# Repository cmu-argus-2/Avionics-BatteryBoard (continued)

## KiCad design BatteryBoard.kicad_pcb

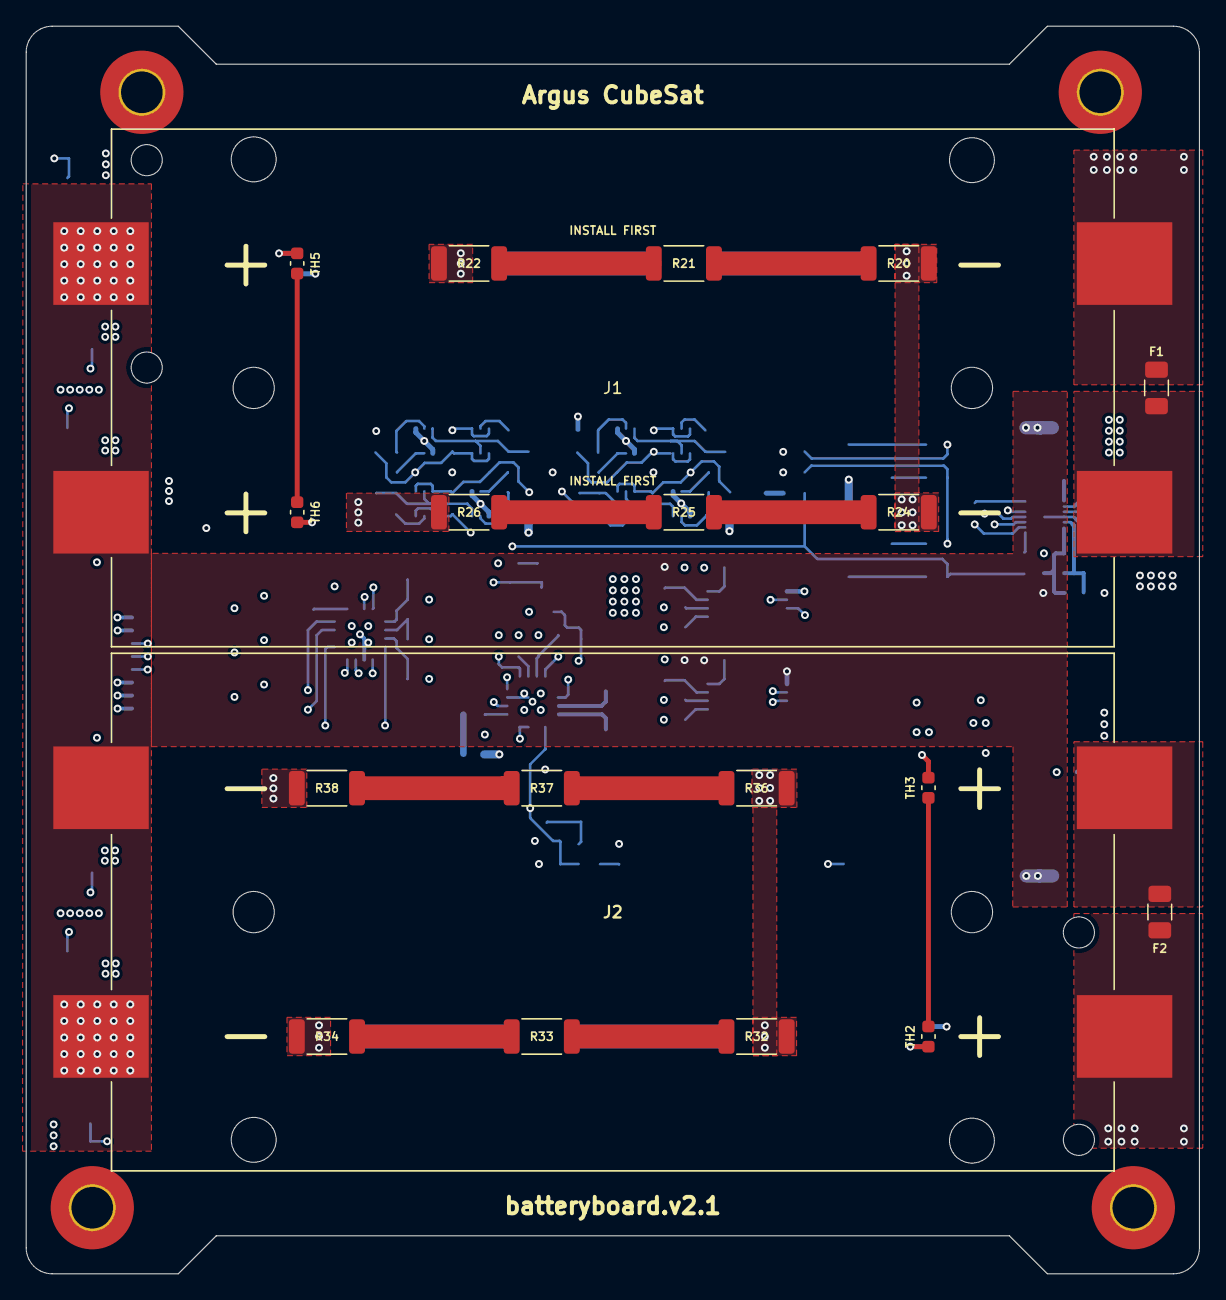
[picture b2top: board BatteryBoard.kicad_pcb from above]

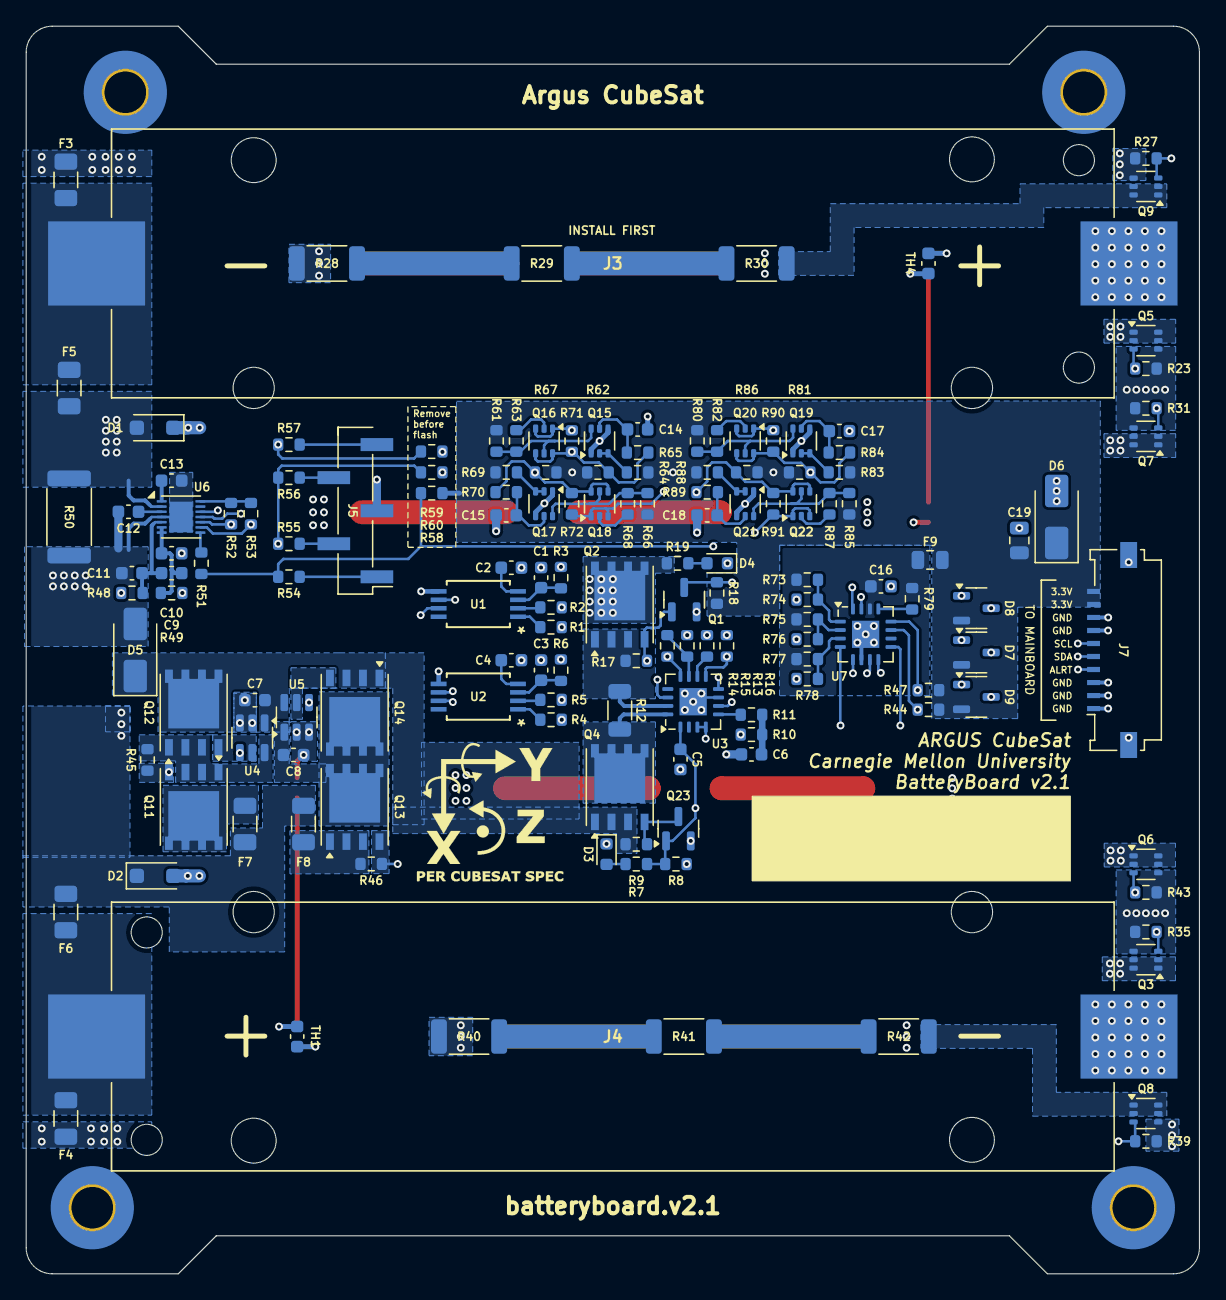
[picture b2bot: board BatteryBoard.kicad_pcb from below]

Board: 4 copper layers, 90.2 x 95.9 mm, 173 parts (149 on the bottom side), 115 nets.

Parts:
C1, C3, C7, C8, C11, C16: 0.1uF; C_0603_1608Metric
C2, C4, C14, C15, C17, C18: 10nF; C_0603_1608Metric
C5, C6: 1uF; C_0603_1608Metric
C9, C10: 1nF; C_0603_1608Metric
C12, C13: 0.47uF; C_0603_1608Metric
C19: 10uF; C_0805_2012Metric
D1, D2: 10V Vrm; D_SOD-123F
D3, D4: GREEN; LED_0603_1608Metric
D5: 10V; D_SMA
D6: 4.7V; D_SMA
D7, D8, D9: MMBD452LT1G; SOT-23-3
F1, F2, F3, F4, F5, F6: 10A; Fuse_1206_3216Metric
F7, F8: 6A; Fuse_1206_3216Metric
F9: 1A; Fuse_0805_2012Metric
H1, H2, H3, H4: MountingHole_Pad; MountingHole_3.2mm_M3_Pad_TopBottom
J1, J2: Keystone-1048; BAT_1048
J3, J4: Keystone-1042; Keystone_1042
J5: Fuel Gauge Programming Header; PinHeader_1x05_P2.54mm_Vertical_SMD_Pin1Left
J7: 200528-0100; Molex_200528-0100_1x10-1MP_P1.00mm_Horizontal
Q1, Q23: IRLML2803; SOT-23
Q2, Q4, Q11, Q12, Q13, Q14: SIRA99DP-T1-GE3; PowerPAK_SO-8_Single
Q3, Q5, Q6, Q7, Q8, Q9: Si1442DH; SOT-363_SC-70-6
Q15, Q17, Q19, Q21: NX3008NBKS; SOT-363_SC-70-6
Q16, Q18, Q20, Q22: MBT2222ADW1T1; SOT-363_SC-70-6
R1, R2, R4, R5, R51: 1k; R_0603_1608Metric
R3, R6: 470R; R_0603_1608Metric
R7, R19: 2.7k; R_0603_1608Metric
R8, R9, R11, R14, R16, R17, R18, R23, R27, R31, R35, R39, R43, R58, R61, R62, R66, R67, R73, R74, R75, R76, R77, R78, R79, R80, R81, R85, R86: 10k; R_0603_1608Metric
R10, R45, R46, R64, R69, R83, R88: 100k; R_0603_1608Metric
R12: 0.05R; R_1206_3216Metric
R13, R59, R60: 0R; R_0603_1608Metric
R15, R52, R53: 30k; R_0603_1608Metric
R20, R21, R22, R24, R25, R26, R28, R29, R30, R32, R33, R34, R36, R37, R38, R40, R41, R42: 10R; R_2010_5025Metric
R44, R47: 470k; R_0603_1608Metric
R48: 10R; R_0603_1608Metric
R49: 100R; R_0603_1608Metric
R50: 10m; R_2512_6332Metric
R54: 51.1k; R_0603_1608Metric
R55, R56, R57: 150R; R_0603_1608Metric
R63, R68, R82, R87: 680R; R_0603_1608Metric
R65, R70, R84, R89: 200k; R_0603_1608Metric
R71, R72, R90, R91: DNI (0R); R_0603_1608Metric
TH1, TH2, TH3, TH4, TH5, TH6: 10k 3435k; C_0603_1608Metric
U1, U2: S-8209AAA-T8T1U; TSSOP8-E-PKG_FT008-A-P-SD-1.2_ABL
U3: MAX4211B/E; QFN-16-1EP_4x4mm_P0.65mm_EP2.1x2.1mm
U4, U5: LTC4412xS6; TSOT-23-6
U6: MAX17205; TDFN-14-1EP_3x3mm_P0.4mm_EP1.78x2.35mm
U7: MAX7310; QFN-16-1EP_4x4mm_P0.65mm_EP2.1x2.1mm

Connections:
+3V3: C19.1, D6.1 (K), D7.2 (K), D8.2 (K), D9.2 (K), F9.2, J7.9, J7.10, R18.2, R44.1, R47.1, R58.2, R61.1, R62.1, R64.1, R66.1, R67.1, R69.1, R80.1, R81.1, R83.1, R85.1, R86.1, R88.1
/Battery Bus Detection/BATT_M: C3.2, C4.2, D1.1 (K), D2.2 (A), J1.2 (POS), J1.4 (POS), J2.1 (NEG), J2.3 (NEG), J3.2 (POS), J4.1 (NEG), R3.1, R49.1, U2.5 (VSS)
/Battery Bus Detection/BATT_N: C1.2, C2.2, C10.2, D1.2 (A), F5.2, R1.2, R2.2, R50.2, U1.5 (VSS), U6.2 (CSP)
/Battery Bus Detection/BATT_P: D2.1 (K), F6.2, F7.1, F8.2, R6.1, R48.1
/Battery Bus Detection/CHARGE_EN: Q11.4 (G), R45.2, U2.7 (CO)
/Battery Bus Detection/DISCHARGE_EN: Q13.4 (G), R46.2, U2.6 (DO)
/Battery Bus Protection/CHARGE_ACTIVE: R44.2, U4.4 (STAT), U7.11 (IO6)
/Battery Bus Protection/DISCHARGE_ACTIVE: R47.2, U5.4 (STAT), U7.12 (IO7)
/Battery Monitor/A: J5.1, R54.2
/Battery Monitor/C: J5.5, R57.2
/Battery Monitor/D: J5.4, R56.2
/Battery Monitor/DQ: J5.2, R55.2
/Battery Monitor/I2C Protection/SCL_DEVICE: Q16.4 (E2), Q16.6 (C1), R59.2, R62.2, R65.1, R71.1
/Battery Monitor/I2C Protection/SDA_DEVICE: Q18.4 (E2), Q18.6 (C1), R60.1, R67.2, R70.1, R72.1
/Battery Monitor/SCL: R57.1, R59.1, U6.11 (SCL)
/Battery Monitor/SDA: R55.1, R56.1, R60.2, U6.12 (SDA)
/Battery Temperature Protection/CB-RESET: R16.2, U3.9 (CIN2-), U7.7 (IO2)
/Battery Temperature Protection/HEATER_ENABLE0: Q5.3 (G), Q7.3 (G), Q9.3 (G), R23.2, R27.2, R31.2, U7.8 (IO3)
/Battery Temperature Protection/HEATER_ENABLE1: Q3.3 (G), Q6.3 (G), Q8.3 (G), R35.2, R39.2, R43.2, U7.9 (IO4)
/Battery Temperature Protection/ON/~OFF: C5.1, Q23.1 (G), R7.1, R8.2, U3.1 (VCC), U7.4 (IO0)
/Battery Temperature Protection/~FAULT: Q1.3 (D), R18.1, U7.5 (IO1)
/IO Expander/AD0: R73.2, R74.1, U7.1 (AD0)
/IO Expander/AD1: R75.2, R76.1, U7.2 (AD1)
/IO Expander/AD2: R77.2, R78.1, U7.3 (AD2)
/IO Expander/SCL: Q20.4 (E2), Q20.6 (C1), R81.2, R84.1, R90.1, U7.15 (SCL)
/IO Expander/SDA: Q22.4 (E2), Q22.6 (C1), R86.2, R89.1, R91.1, U7.16 (SDA)
/Interfaces/ALERT: D9.3 (common), J7.4, R51.2, R54.1, R58.1
/Interfaces/SCL_BUS: D8.3 (common), J7.6, Q16.1 (E1), Q16.3 (C2), Q20.1 (E1), Q20.3 (C2), R71.2, R90.2
/Interfaces/SDA_BUS: D7.3 (common), J7.5, Q18.1 (E1), Q18.3 (C2), Q22.1 (E1), Q22.3 (C2), R72.2, R91.2
GND: C5.2, C14.2, C15.2, C16.2, C17.2, C18.2, C19.2, D3.1 (K), D4.1 (K), D6.2 (A), D7.1 (A), D8.1 (A), D9.1 (A), H1.1, H2.1, H3.1, H4.1, J7.1, J7.2, J7.3, J7.7, J7.8, J7.MP (MountPin), Q1.2 (S), Q15.1 (S), Q15.4 (S), Q17.1 (S), Q17.4 (S), Q19.1 (S), Q19.4 (S), Q21.1 (S), Q21.4 (S), Q23.2 (S), R8.1, R10.1, R15.1, R16.1, R74.2, R76.2, R78.2, U3.7 (GND), U3.17 (GND), U7.6 (GND), U7.17 (GND)
unnamed: C6.1, R10.2, R11.2
unnamed: D3.2 (A), R7.2
unnamed: D4.2 (A), R19.1
unnamed: F1.1, J1.1 (NEG)
unnamed: F1.2, F3.1, J1.3 (NEG)
unnamed: F2.1, J2.2 (POS)
unnamed: F2.2, F4.1, J2.4 (POS)
unnamed: F8.1, Q13.1 (S), Q13.2 (S), Q13.3 (S), R46.1
unnamed: F3.2, F5.1, J3.1 (NEG)
unnamed: F4.2, F6.1, J4.2 (POS)
unnamed: Q1.1 (G), Q2.4 (G), R17.1, U3.3 (LE), U3.4 (COUT1), U3.6 (COUT2)
unnamed: Q3.1 (D), Q3.2 (D), Q3.5 (D), Q3.6 (D), R34.1
unnamed: Q4.5 (D), R12.1, U3.16 (RS+)
unnamed: Q5.1 (D), Q5.2 (D), Q5.5 (D), Q5.6 (D), R22.1
unnamed: Q6.1 (D), Q6.2 (D), Q6.5 (D), Q6.6 (D), R38.1
unnamed: Q7.1 (D), Q7.2 (D), Q7.5 (D), Q7.6 (D), R26.1
unnamed: Q8.1 (D), Q8.2 (D), Q8.5 (D), Q8.6 (D), R42.1
unnamed: Q9.1 (D), Q9.2 (D), Q9.5 (D), Q9.6 (D), R30.1
unnamed: F7.2, Q11.5 (D)
unnamed: Q12.4 (G), U4.5 (GATE)
unnamed: C8.1, Q13.5 (D), Q14.5 (D), U5.1 (VIN)
unnamed: Q14.4 (G), U5.5 (GATE)
unnamed: Q15.6 (D), Q16.5 (B2), R61.2, R63.2
unnamed: Q15.2 (G), Q15.3 (D), R64.2
unnamed: C14.1, Q15.5 (G), R65.2
unnamed: Q16.2 (B1), R63.1
unnamed: Q17.6 (D), Q18.5 (B2), R66.2, R68.2
unnamed: Q17.2 (G), Q17.3 (D), R69.2
unnamed: C15.1, Q17.5 (G), R70.2
unnamed: Q18.2 (B1), R68.1
unnamed: Q19.6 (D), Q20.5 (B2), R80.2, R82.2
unnamed: Q19.2 (G), Q19.3 (D), R83.2
unnamed: C17.1, Q19.5 (G), R84.2
unnamed: Q20.2 (B1), R82.1
unnamed: Q21.6 (D), Q22.5 (B2), R85.2, R87.2
unnamed: Q21.2 (G), Q21.3 (D), R88.2
unnamed: C18.1, Q21.5 (G), R89.2
unnamed: Q22.2 (B1), R87.1
unnamed: Q4.4 (G), Q23.3 (D), R9.1
unnamed: R20.1, R21.2
unnamed: R21.1, R22.2
unnamed: R24.1, R25.2
unnamed: R25.1, R26.2
unnamed: R28.1, R29.2
unnamed: R29.1, R30.2
unnamed: R32.1, R33.2
unnamed: R33.1, R34.2
unnamed: R36.1, R37.2
unnamed: R37.1, R38.2
unnamed: R40.1, R41.2
unnamed: R41.1, R42.2
unnamed: TH1.2, TH2.1
unnamed: TH2.2, TH3.1
unnamed: TH4.2, TH5.1
unnamed: TH5.2, TH6.1
unnamed: C2.1, U1.4 (CDT)
unnamed: R4.2, U1.7 (CO)
unnamed: R1.1, U1.1 (CTLC)
unnamed: R2.1, U1.2 (CTLD)
unnamed: R5.2, U1.6 (DO)
unnamed: C1.1, R3.2, U1.3 (VDD)
unnamed: C4.1, U2.4 (CDT)
unnamed: R4.1, U2.1 (CTLC)
unnamed: R5.1, U2.2 (CTLD)
unnamed: C3.1, R6.2, U2.3 (VDD)
unnamed: R13.1, U3.10 (CIN1+)
unnamed: R14.1, R15.2, U3.11 (CIN1-)
unnamed: R14.2, U3.8 (CIN2+), U3.12 (REF)
unnamed: R11.1, U3.5 (INHIBIT)
unnamed: R13.2, U3.14 (IOUT)
unnamed: Q2.1 (S), Q2.2 (S), Q2.3 (S), R12.2, R17.2, U3.15 (RS-)
unnamed: Q11.1 (S), Q11.2 (S), Q11.3 (S), Q12.1 (S), Q12.2 (S), Q12.3 (S), R45.1, U4.6 (SENSE)
unnamed: R53.2, TH4.1, U6.9 (AIN1)
unnamed: R52.2, TH1.1, U6.10 (AIN2)
unnamed: R51.1, U6.8 (ALRT1)
unnamed: C9.2, C10.1, R49.2, U6.6 (CELL2), U6.7 (CELL1)
unnamed: C12.1, U6.3 (REG2)
unnamed: C13.1, U6.1 (REG3)
unnamed: R52.1, R53.1, U6.14 (THRM)
unnamed: C9.1, C11.1, R48.2, U6.5 (VBATT)
unnamed: C16.1, F9.1, R73.1, R75.1, R77.1, R79.2, U7.14 (V+)
unnamed: R79.1, U7.13 (~RESET)
SYSTEM_VDD: C7.1, D5.1 (K), Q4.1 (S), Q4.2 (S), Q4.3 (S), Q12.5 (D), Q14.1 (S), Q14.2 (S), Q14.3 (S), R9.2, U4.1 (VIN), U5.6 (SENSE)
SYSTEM_VSS: C7.2, C8.2, C11.2, C12.2, C13.2, D5.2 (A), J5.3, Q3.4 (S), Q5.4 (S), Q6.4 (S), Q7.4 (S), Q8.4 (S), Q9.4 (S), R23.1, R27.1, R31.1, R35.1, R39.1, R43.1, R50.1, TH3.2, TH6.2, U4.2 (GND), U4.3 (CTL), U5.2 (GND), U5.3 (CTL), U6.4 (CSN), U6.15 (GND)
VBUS: C6.2, Q2.5 (D), R19.2, R20.2, R24.2, R28.2, R32.2, R36.2, R40.2

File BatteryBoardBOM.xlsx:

Reference | Value | Datasheet | Footprint | Qty | DNP | MFR Part Number
C1,C3,C7,C8,C11 | 0.1uF | ~ | Capacitor_SMD:C_0603_1608Metric | 5 |  | CL10B104KA8NNNC | 25
C2,C4,C14,C15 | 10nF | ~ | Capacitor_SMD:C_0603_1608Metric | 4 |  | CL10B103KO8WPNC | 20
C9,C10 | 1nF | ~ | Capacitor_SMD:C_0603_1608Metric | 2 |  | C0603C102J8HACAUTO | 10
C12,C13 | 0.47uF | ~ | Capacitor_SMD:C_0603_1608Metric | 2 |  | CL10B474KO8VPJC | 10
C19 | 10uF | ~ | Capacitor_SMD:C_0805_2012Metric | 1 |  | GRM21BR71A106KA73L | 5
D1,D2 | BAT60JFILM | ~ | Diode_SMD:D_SOD-323_HandSoldering | 2 |  | BAT60JFILM | 10
D3,D4,D10 | GREEN | ~ | LED_SMD:LED_0603_1608Metric | 3 |  | 150060GS75000 | 15
D5 | 10V | ~ | Diode_SMD:D_SMA | 1 |  | PTVS10VZ1USKYL | 5
F1,F2,F3,F4,F5,F6,F9 | 5A | ~ | Fuse:Fuse_1206_3216Metric | 7 |  | C1F 5 | 35
F7,F8 | 6A | ~ | Fuse:Fuse_1206_3216Metric | 2 |  | 0685T6000-01 | 10
F10,F11 | 2A | ~ | Fuse:Fuse_1206_3216Metric | 2 |  | C1F 2 | 10
J1,J2 | Keystone-1048 |  | Argus-Misc:BAT_1048 | 2 |  | Keystone-1048 | 10
J3,J4 | Keystone-1042 |  | Argus-Misc:Keystone_1042 | 2 |  | Keystone-1042 | 10
J5 | Fuel Gauge Programming Header | ~ | Connector_PinHeader_2.54mm:PinHeader_1x05_P2.54mm_Vertical_SMD_Pin1Left | 1 |  | TSM-105-01-L-SV-P-TR | 5
J6 | 282834-4 | ~ | TerminalBlock_TE-Connectivity:TerminalBlock_TE_282834-4_1x04_P2.54mm_Horizontal | 1 |  | 282834-4 | 5
J7 | 200528-0100 | ~ | Connector_FFC-FPC:Molex_200528-0100_1x10-1MP_P1.00mm_Horizontal | 1 |  | 200528-0100 | 5
Q1,Q10,Q23 | IRLML2803 |  | Package_TO_SOT_SMD:SOT-23 | 3 |  | IRLML2803 | 15
Q2,Q4,Q11,Q12,Q13,Q14,Q19 | SIRA99DP-T1-GE3 | https://www.vishay.com/docs/65596/si7141dp.pdf | Package_SO:PowerPAK_SO-8_Single | 7 |  | SIRA99DP-T1-GE3 | 35
Q15,Q17 | NX3008NBKS | ~ | Package_TO_SOT_SMD:SOT-363_SC-70-6 | 2 |  | NX3008NBKS | 10
Q16,Q18 | MBT2222ADW1T1 | http://www.onsemi.com/pub_link/Collateral/MBT2222ADW1T1-D.PDF | Package_TO_SOT_SMD:SOT-363_SC-70-6 | 2 |  | MBT2222ADW1T1 | 10
R1,R2,R4,R5,R7,R11,R15,R51 | 1k | ~ | Resistor_SMD:R_0603_1608Metric | 8 |  | RC0603FR-071KL | 40
R3,R6 | 470R | ~ | Resistor_SMD:R_0603_1608Metric | 2 |  | RC0603JR-07470RL | 10
R8,R9,R10,R12,R14,R16,R58,R61,R62,R66,R67 | 10k | ~ | Resistor_SMD:R_0603_1608Metric | 11 |  | RMCF0603JT10K0 | 55
R13,R17,R19 | 2.7k | ~ | Resistor_SMD:R_0603_1608Metric | 3 |  | RC0603JR-072K7L | 15
R20,R21,R22,R24,R25,R26,R28,R29,R30,R32,R33,R34,R36,R37,R38,R40,R41,R42 | 10R | ~ | Resistor_SMD:R_2010_5025Metric | 18 |  | 350210RJT | 90
R48 | 10R | ~ | Resistor_SMD:R_0603_1608Metric | 1 |  | ERJ-3EKF10R0V | 5
R44,R47 | 470k | ~ | Resistor_SMD:R_0603_1608Metric | 2 |  | RMCF0603FT470K | 10
R45,R46,R64,R69 | 100k | ~ | Resistor_SMD:R_0603_1608Metric | 4 |  | ERJ-3EKF1003V | 20
R49 | 100R | ~ | Resistor_SMD:R_0603_1608Metric | 1 |  | ERJ-3EKF1000V | 5
R50 | 10m | ~ | Resistor_SMD:R_2512_6332Metric | 1 |  | CRA2512-FZ-R010ELF | 5
R52,R53 | 30k | ~ | Resistor_SMD:R_0603_1608Metric | 2 |  | ERA-3AEB303V | 10
R54 | 51.1k | ~ | Resistor_SMD:R_0603_1608Metric | 1 |  | RC0603FR-0751K1L | 5
R55,R56,R57 | 150R | ~ | Resistor_SMD:R_0603_1608Metric | 3 |  | ERA-3AEB151V | 15
R59,R60 | 0R | ~ | Resistor_SMD:R_0603_1608Metric | 2 |  | RC0603JR-070RL | 10
R63,R68 | 680R | ~ | Resistor_SMD:R_0603_1608Metric | 2 |  | RC0603JR-07680RL | 10
R65,R70 | 200k | ~ | Resistor_SMD:R_0603_1608Metric | 2 |  | ERA-3AEB204V | 10
R71,R72 | 0R | ~ | Resistor_SMD:R_0603_1608Metric | 2 | DNP | RC0603JR-070RL | 10
TH1,TH2,TH3,TH4,TH5,TH6 | 10k 3435k | ~ | Capacitor_SMD:C_0603_1608Metric | 6 |  | NTCS0603E3103JLT | 30
U1,U2 | S-8209AAA-T8T1U | S-8209AAA-T8T1U | Argus-IC:TSSOP8-E-PKG_FT008-A-P-SD-1.2_ABL | 2 |  |  | 10
U3,U7 | D5V0P4UR6SO | http://www.onsemi.com/pub/Collateral/SRV05-4-D.PDF | Package_TO_SOT_SMD:SOT-23-6 | 2 |  | D5V0P4UR6SO | 10
U4,U5 | LTC4412xS6 | https://www.analog.com/media/en/technical-documentation/data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 | Package_TO_SOT_SMD:TSOT-23-6 | 2 |  | LTC4412ES6#TRMPBF | 10
U6 | MAX17205 |  | Package_DFN_QFN:TDFN-14-1EP_3x3mm_P0.4mm_EP1.78x2.35mm | 1 |  |  | 5

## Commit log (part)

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2024-09-17 Added gitignore
2024-09-17 Added KiCad libs
2024-09-18 Initial project setup
2024-09-21 First pass at battery board schematics
2024-09-26 First pass at new schematics and board
2024-09-26 Repoured polys
2024-09-26 Updated footprint to follow PC/104
2024-09-29 Refactored schematics and silkscreen
2024-09-29 Updated submodule
2024-09-29 Removed backups
2024-09-29 Updated footprint
2024-09-29 added thermal relief connection for fpc connector
2024-10-02 Changes for lib refactor
2024-10-04 Fixes from feedback
2024-10-05 Added more silkscreen for mainboard connector
2024-10-06 Updated silkscreen
2024-10-07 Minor DRC Fixes, exported BOM and STEP model
2024-11-19 Updated version to v2.1
2024-11-19 Removed submodule KiCad-Libraries
2024-11-19 Re-add Kicad-Libraries
2024-11-19 idek
2024-12-20 v2.1 (v3?) Partial Updates
2024-12-21 Silkscreen cleanup
2025-01-15 More updates
2025-01-27 Finalized updates with recommendations and exported files
2025-02-04 Added MAX17205 Breakout
2025-02-11 uncommitted changes
2025-02-26 Added MAX17205 Config Files
2025-04-01 Updated board outline and power pinout
2025-04-01 Fixed programmer board libs
2025-04-01 Increased pad size for power cables
2025-04-12 Re-export STEP Files
2025-04-19 Updated FPC connector
2025-06-17 v3.1 Updates
2025-06-17 Idk some changes
2025-06-19 Fixed STEP model thickness
2026-01-21 Local Stash
2026-01-21 kicad pull
2026-04-14 v3.2 Updates
    Added 0ohm bypass. Opto-isolated heater enables
2026-04-14 Export STEP and BOM
